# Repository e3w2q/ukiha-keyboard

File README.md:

# Ukiha

Small key pitch 5x12 ortholinear keyboard.

## What is the Ukiha?

The Ukiha is a 5x12 ortholinear keyboard like the Preonic and JJ50, but with a smaller key pitch of 16mm instead of 19.05mm.

I like expantable keyboard boards like [SU120](https://github.com/e3w2q/su120-keyboard) and [te96](https://github.com/e3w2q/te96-keyboard), but in this case I designed a keyboard that I genuinely wanted.

The *Ukiha* (浮葉) means "floating leaf" and is taken from the Japanese classic, *Pillow Book* (枕草子).

In the book, there is an example of a very small floating lotus leaf taken from a pond as a lovely thing.

うつくしきもの。(中略) 蓮の浮葉のいとちひさきを、池より取りあげたる。(枕草子 第百五十一段より)

## Why open source?

Anyone interested in small key pitch keyboard could try.

## Customizability

The 4 keys in the middle of the bottom row can be replaced with 2U.

You can take off the top row and make it into a 4x12 keyboard like Planck and JJ40.

## Link

[Hardware data (PCB)](pcb/)

[Firmware](https://github.com/e3w2q/qmk_firmware/tree/e3w2q/keyboards/e3w2q/ukiha)

[PCBの入手方法](doc/pcb_order_guide_jp.md)

[パーツリスト](doc/bom_list_jp.md)

[ビルドガイド](doc/readme_jp.md)

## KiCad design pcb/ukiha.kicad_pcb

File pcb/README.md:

# Ukiha PCB Data

## Schematic
[Schematic PDF](../doc/schematic.pdf?raw=true)

## PCB Layout

## Acrylic Layout

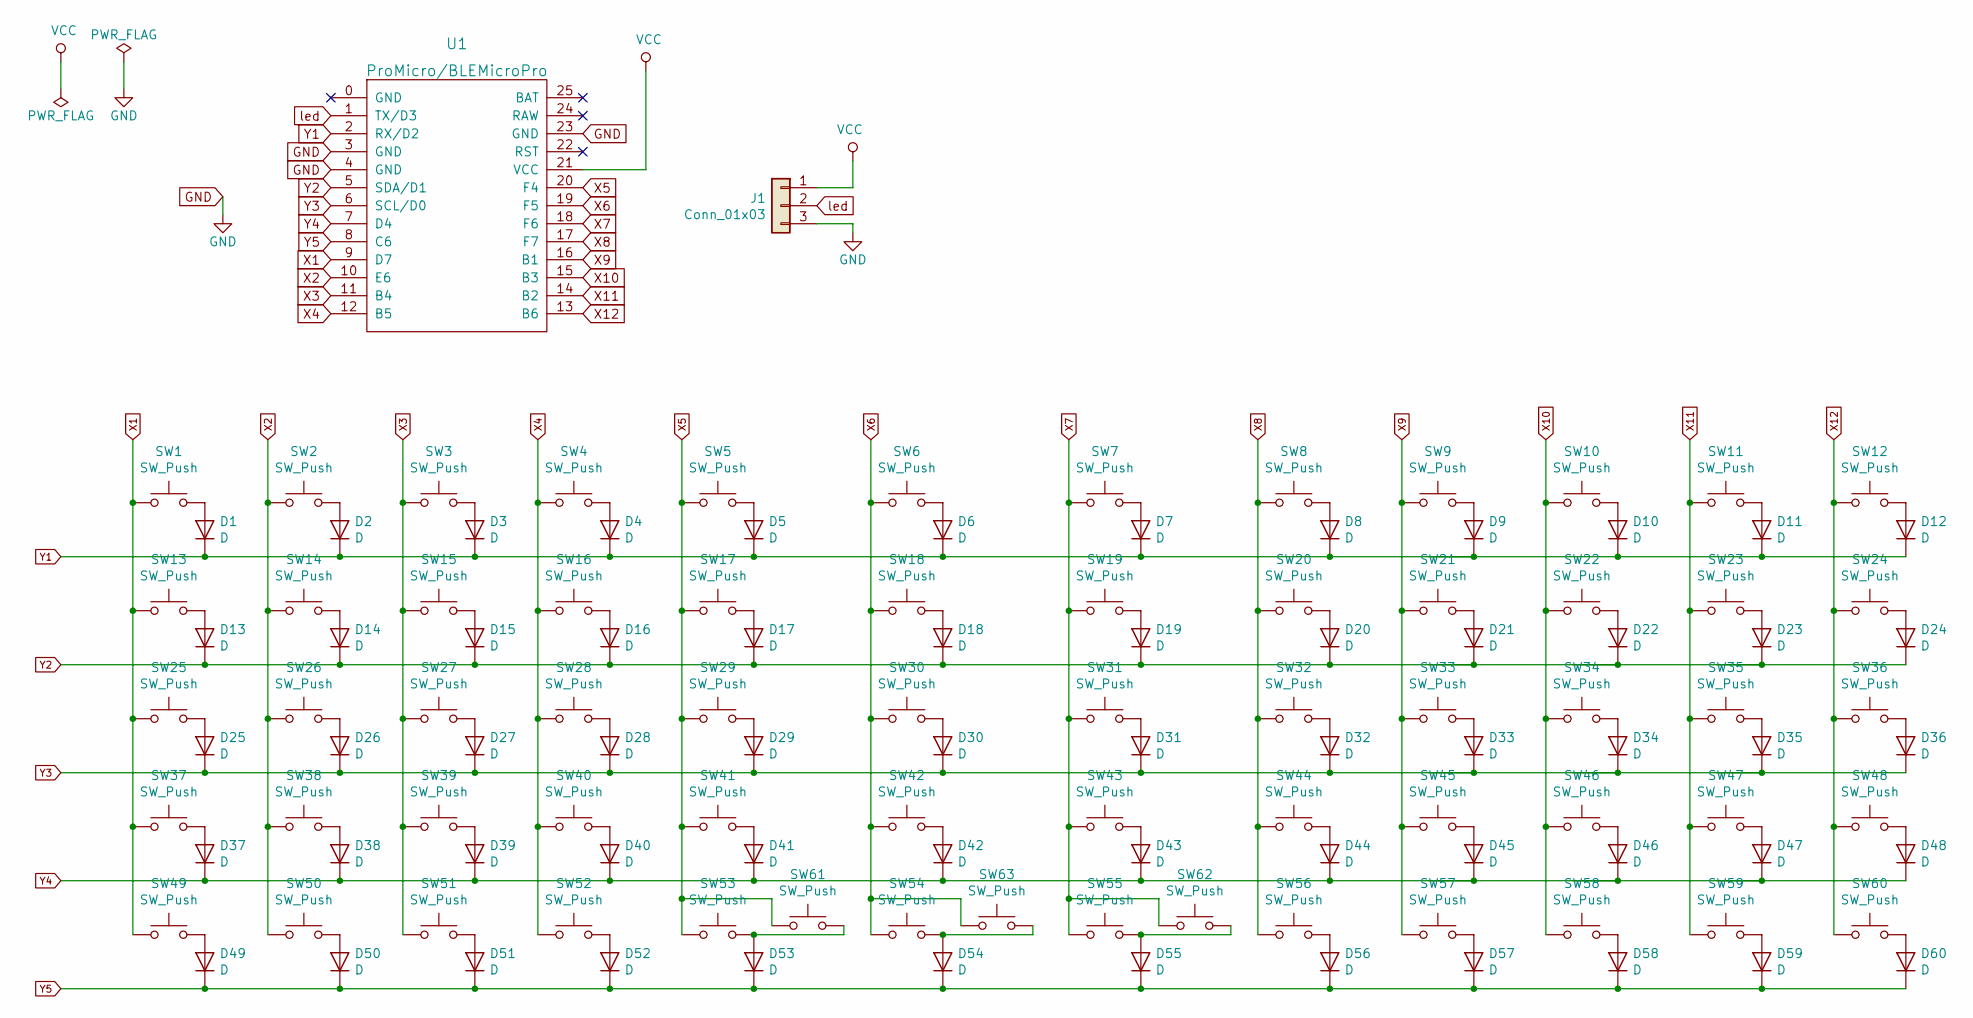
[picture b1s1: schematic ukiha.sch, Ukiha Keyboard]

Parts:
D1, D2, D3, D4, D5, D6, D7, D8, D9, D10, D11, D12, D13, D14, D15, D16, D17, D18, D19, D20, D21, D22, D23, D24, D25, D26, D27, D28, D29, D30, D31, D32, D33, D34, D35, D36, D37, D38, D39, D40, D41, D42, D43, D44, D45, D46, D47, D48, D49, D50, D51, D52, D53, D54, D55, D56, D57, D58, D59, D60: D; diode_SMD
J1: Conn_01x03; StripLED_rev2
SW1, SW2, SW3, SW4, SW5, SW6, SW7, SW8, SW9, SW10, SW11, SW12, SW13, SW14, SW15, SW16, SW17, SW18, SW19, SW20, SW21, SW22, SW23, SW24, SW25, SW26, SW27, SW28, SW29, SW30, SW31, SW32, SW33, SW34, SW35, SW36, SW37, SW38, SW39, SW40, SW41, SW42, SW43, SW44, SW45, SW46, SW47, SW48, SW49, SW50, SW51, SW52, SW53, SW54, SW55, SW56, SW57, SW58, SW59, SW60, SW61, SW62, SW63: SW_Push; CherryMX_MidHeight_16mm_rev2
U1: ProMicro/BLEMicroPro; ArduinoProMicro_ConThrough

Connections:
GND: J1.3, U1.3 (GND), U1.4 (GND), U1.23 (GND)
unnamed: D1.2 (A), SW1.2
unnamed: D2.2 (A), SW2.2
unnamed: D3.2 (A), SW3.2
unnamed: D4.2 (A), SW4.2
unnamed: D5.2 (A), SW5.2
unnamed: D6.2 (A), SW6.2
unnamed: D7.2 (A), SW7.2
unnamed: D8.2 (A), SW8.2
unnamed: D9.2 (A), SW9.2
unnamed: D10.2 (A), SW10.2
unnamed: D11.2 (A), SW11.2
unnamed: D12.2 (A), SW12.2
unnamed: D13.2 (A), SW13.2
unnamed: D14.2 (A), SW14.2
unnamed: D15.2 (A), SW15.2
unnamed: D16.2 (A), SW16.2
unnamed: D17.2 (A), SW17.2
unnamed: D18.2 (A), SW18.2
unnamed: D19.2 (A), SW19.2
unnamed: D20.2 (A), SW20.2
unnamed: D21.2 (A), SW21.2
unnamed: D22.2 (A), SW22.2
unnamed: D23.2 (A), SW23.2
unnamed: D24.2 (A), SW24.2
unnamed: D25.2 (A), SW25.2
unnamed: D26.2 (A), SW26.2
unnamed: D27.2 (A), SW27.2
unnamed: D28.2 (A), SW28.2
unnamed: D29.2 (A), SW29.2
unnamed: D30.2 (A), SW30.2
unnamed: D31.2 (A), SW31.2
unnamed: D32.2 (A), SW32.2
unnamed: D33.2 (A), SW33.2
unnamed: D34.2 (A), SW34.2
unnamed: D35.2 (A), SW35.2
unnamed: D36.2 (A), SW36.2
unnamed: D37.2 (A), SW37.2
unnamed: D38.2 (A), SW38.2
unnamed: D39.2 (A), SW39.2
unnamed: D40.2 (A), SW40.2
unnamed: D41.2 (A), SW41.2
unnamed: D42.2 (A), SW42.2
unnamed: D43.2 (A), SW43.2
unnamed: D44.2 (A), SW44.2
unnamed: D45.2 (A), SW45.2
unnamed: D46.2 (A), SW46.2
unnamed: D47.2 (A), SW47.2
unnamed: D48.2 (A), SW48.2
unnamed: D49.2 (A), SW49.2
unnamed: D50.2 (A), SW50.2
unnamed: D51.2 (A), SW51.2
unnamed: D52.2 (A), SW52.2
unnamed: D53.2 (A), SW53.2, SW61.2
unnamed: D54.2 (A), SW54.2, SW63.2
unnamed: D55.2 (A), SW55.2, SW62.2
unnamed: D56.2 (A), SW56.2
unnamed: D57.2 (A), SW57.2
unnamed: D58.2 (A), SW58.2
unnamed: D59.2 (A), SW59.2
unnamed: D60.2 (A), SW60.2
VCC: J1.1, U1.21 (VCC)
X1: SW1.1, SW13.1, SW25.1, SW37.1, SW49.1, U1.9 (D7)
X2: SW2.1, SW14.1, SW26.1, SW38.1, SW50.1, U1.10 (E6)
X3: SW3.1, SW15.1, SW27.1, SW39.1, SW51.1, U1.11 (B4)
X4: SW4.1, SW16.1, SW28.1, SW40.1, SW52.1, U1.12 (B5)
X5: SW5.1, SW17.1, SW29.1, SW41.1, SW53.1, SW61.1, U1.20 (F4)
X6: SW6.1, SW18.1, SW30.1, SW42.1, SW54.1, SW63.1, U1.19 (F5)
X7: SW7.1, SW19.1, SW31.1, SW43.1, SW55.1, SW62.1, U1.18 (F6)
X8: SW8.1, SW20.1, SW32.1, SW44.1, SW56.1, U1.17 (F7)
X9: SW9.1, SW21.1, SW33.1, SW45.1, SW57.1, U1.16 (B1)
X10: SW10.1, SW22.1, SW34.1, SW46.1, SW58.1, U1.15 (B3)
X11: SW11.1, SW23.1, SW35.1, SW47.1, SW59.1, U1.14 (B2)
X12: SW12.1, SW24.1, SW36.1, SW48.1, SW60.1, U1.13 (B6)
Y1: D1.1 (K), D2.1 (K), D3.1 (K), D4.1 (K), D5.1 (K), D6.1 (K), D7.1 (K), D8.1 (K), D9.1 (K), D10.1 (K), D11.1 (K), D12.1 (K), U1.2 (RX/D2)
Y2: D13.1 (K), D14.1 (K), D15.1 (K), D16.1 (K), D17.1 (K), D18.1 (K), D19.1 (K), D20.1 (K), D21.1 (K), D22.1 (K), D23.1 (K), D24.1 (K), U1.5 (SDA/D1)
Y3: D25.1 (K), D26.1 (K), D27.1 (K), D28.1 (K), D29.1 (K), D30.1 (K), D31.1 (K), D32.1 (K), D33.1 (K), D34.1 (K), D35.1 (K), D36.1 (K), U1.6 (SCL/D0)
Y4: D37.1 (K), D38.1 (K), D39.1 (K), D40.1 (K), D41.1 (K), D42.1 (K), D43.1 (K), D44.1 (K), D45.1 (K), D46.1 (K), D47.1 (K), D48.1 (K), U1.7 (D4)
Y5: D49.1 (K), D50.1 (K), D51.1 (K), D52.1 (K), D53.1 (K), D54.1 (K), D55.1 (K), D56.1 (K), D57.1 (K), D58.1 (K), D59.1 (K), D60.1 (K), U1.8 (C6)
led: J1.2, U1.1 (TX/D3)

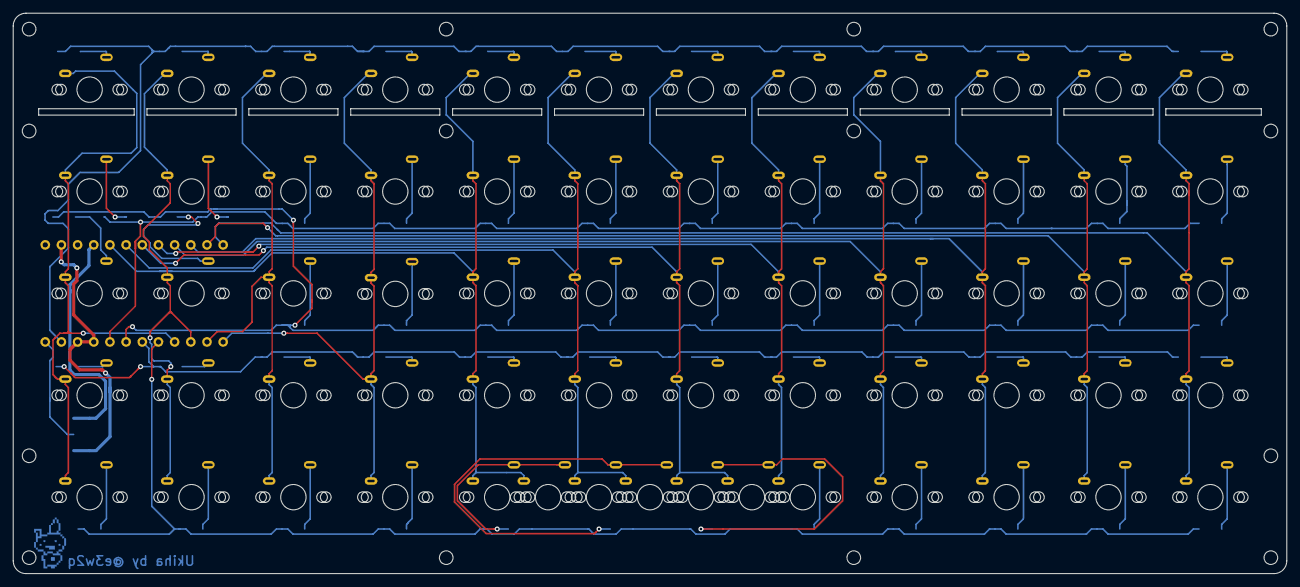
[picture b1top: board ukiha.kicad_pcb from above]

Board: 2 copper layers, 200.0 x 88.0 mm, 125 parts (1 on the bottom side), 80 nets.

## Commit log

2020-10-22 1st commit
2020-10-24 Add 48 key middle plate
2020-11-03 Fix PCB
2020-11-03 Fix size
2020-11-05 Update docs
2020-11-08 Add readme_rev1_jp
2021-03-10 Fix screw hole position

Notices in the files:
README.md:
License: MIT
